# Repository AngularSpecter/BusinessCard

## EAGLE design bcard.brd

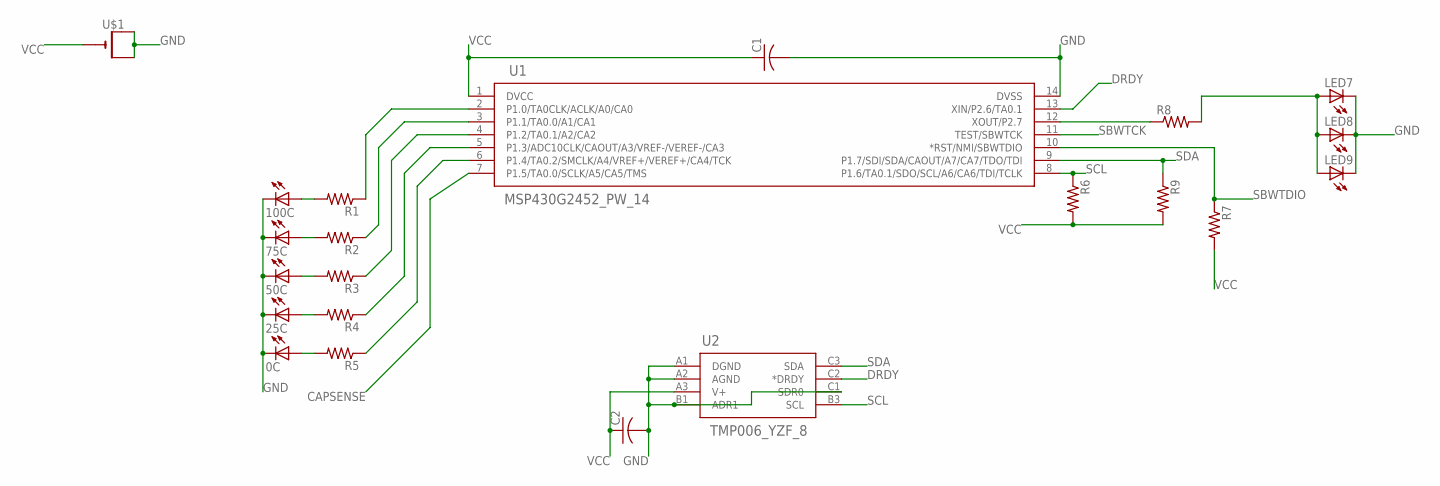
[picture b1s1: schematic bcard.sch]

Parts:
0C, 25C, 50C, 75C, 100C: LEDCHIP-LED0805; CHIP-LED0805
C1, C2: C-USC0805; C0805
LED7, LED8, LED9: LEDCHIP-LED0805; CHIP-LED0805
R1, R2, R3, R4, R5, R6, R7, R8, R9: R-US_R0805; R0805
U1: MSP430G2452_PW_14; PW14
U2: TMP006_YZF_8; YZF8
U$1: CR1220SMT; CR1220-SMD

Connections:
CAPSENSE: U1.7 (P1.5/TA0.0/SCLK/A5/CA5/TMS)
DRDY: U1.13 (XIN/P2.6/TA0.1), U2.C2 (*DRDY)
FLASH: R8.1, U1.12 (XOUT/P2.7)
FLASHVCC: LED7.A, LED8.A, LED9.A, R8.2
GND: 0C.C, 25C.C, 50C.C, 75C.C, 100C.C, C1.2, C2.2, LED7.C, LED8.C, LED9.C, U1.14 (DVSS), U2.A1 (DGND), U2.A2 (AGND), U2.B1 (ADR1), U2.C1 (SDR0), U$1.+$1 (+), U$1.+$2 (+1)
LED1: R1.1, U1.2 (P1.0/TA0CLK/ACLK/A0/CA0)
LED1.1: 100C.A, R1.2
LED2: R2.1, U1.3 (P1.1/TA0.0/A1/CA1)
LED2.1: 75C.A, R2.2
LED3: R3.1, U1.4 (P1.2/TA0.1/A2/CA2)
LED3.1: 50C.A, R3.2
LED4: R4.1, U1.5 (P1.3/ADC10CLK/CAOUT/A3/VREF-/VEREF-/CA3)
LED4.1: 25C.A, R4.2
LED5: R5.1, U1.6 (P1.4/TA0.2/SMCLK/A4/VREF+/VEREF+/CA4/TCK)
LED5.1: 0C.A, R5.2
SBWTCK: U1.11 (TEST/SBWTCK)
SBWTDIO: R7.1, U1.10 (*RST/NMI/SBWTDIO)
SCL: R6.1, U1.8 (P1.6/TA0.1/SDO/SCL/A6/CA6/TDI/TCLK), U2.B3 (SCL)
SDA: R9.1, U1.9 (P1.7/SDI/SDA/CAOUT/A7/CA7/TDO/TDI), U2.C3 (SDA)
VCC: C1.1, C2.1, R6.2, R7.2, R9.2, U1.1 (DVCC), U2.A3 (V+), U$1.-

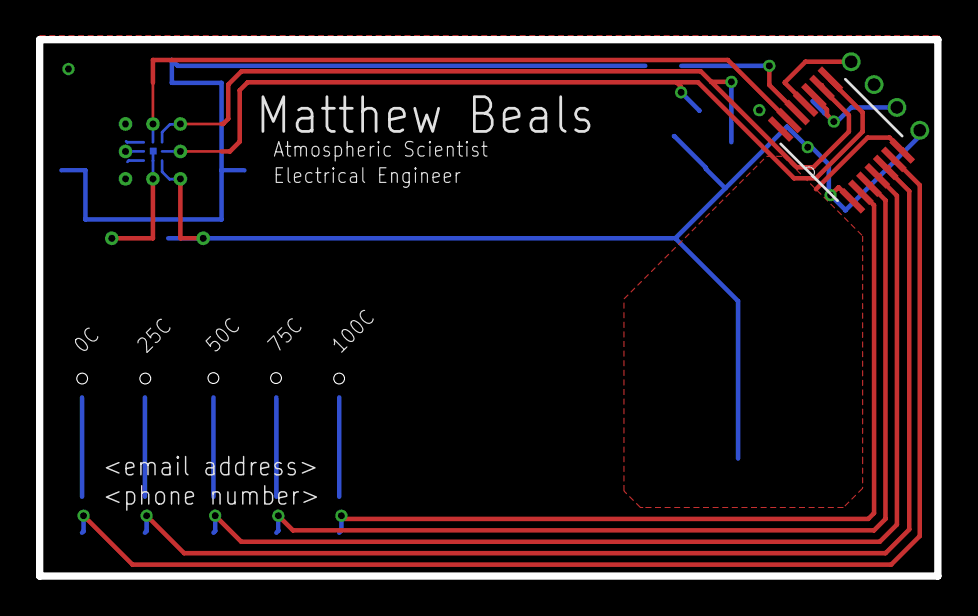
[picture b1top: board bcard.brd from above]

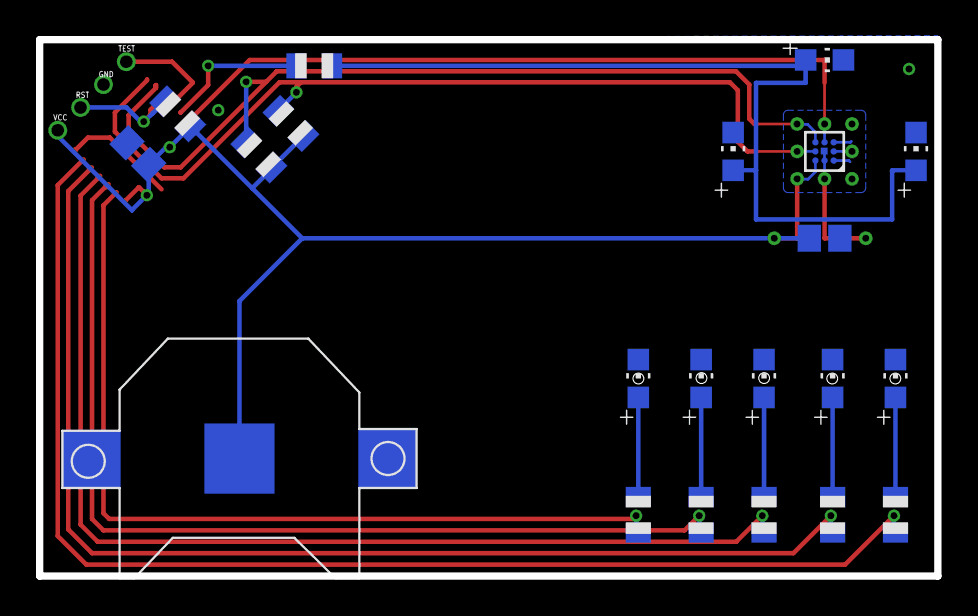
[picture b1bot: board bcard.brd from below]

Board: 2 copper layers, 49.9 x 29.8 mm, 22 parts (21 on the bottom side), 18 nets.
